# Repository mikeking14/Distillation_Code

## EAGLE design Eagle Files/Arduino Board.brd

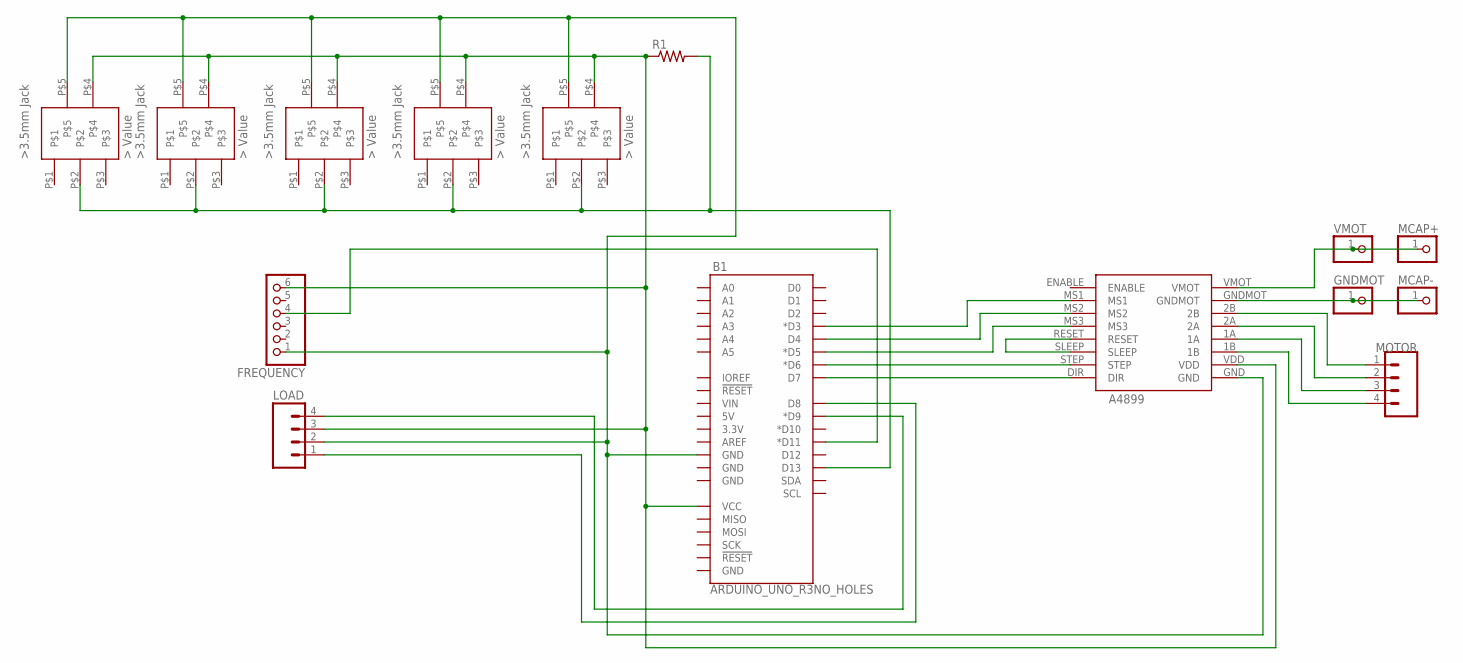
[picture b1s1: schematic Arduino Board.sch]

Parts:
3.5MM_JACK1, 3.5MM_JACK2, 3.5MM_JACK3, 3.5MM_JACK4, 3.5MM_JACK5: 3.5MM_JACK
A4899_1: A4899
B1: ARDUINO_UNO_R3NO_HOLES; ARDUINO_R3_NO_HOLES
FREQUENCY: PINHD-1X6; 1X06
GNDMOT: PINHD-1X1; 1X01
LOAD: M04PTH; 1X04
MCAP+: PINHD-1X1; 1X01
MCAP-: PINHD-1X1; 1X01
MOTOR: M04PTH; 1X04
R1: R-US_0204/5; 0204/5
VMOT: PINHD-1X1; 1X01

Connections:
unnamed: 3.5MM_JACK1.P$5, 3.5MM_JACK2.P$5, 3.5MM_JACK3.P$5, 3.5MM_JACK4.P$5, 3.5MM_JACK5.P$5, A4899_1.GND, B1.GND@4 (GND), FREQUENCY.1, LOAD.2
unnamed: 3.5MM_JACK1.P$2, 3.5MM_JACK2.P$2, 3.5MM_JACK3.P$2, 3.5MM_JACK4.P$2, 3.5MM_JACK5.P$2, B1.D13, R1.2
unnamed: A4899_1.1B, MOTOR.4
unnamed: B1.D11 (*D11), FREQUENCY.4
unnamed: B1.D9 (*D9), LOAD.4
unnamed: B1.D8, LOAD.1
unnamed: A4899_1.VMOT, MCAP+.1, VMOT.1
unnamed: A4899_1.GNDMOT, GNDMOT.1, MCAP-.1
unnamed: A4899_1.2B, MOTOR.1
unnamed: A4899_1.2A, MOTOR.2
unnamed: A4899_1.1A, MOTOR.3
unnamed: A4899_1.MS3, B1.D5 (*D5)
unnamed: A4899_1.RESET, A4899_1.SLEEP
unnamed: 3.5MM_JACK1.P$4, 3.5MM_JACK2.P$4, 3.5MM_JACK3.P$4, 3.5MM_JACK4.P$4, 3.5MM_JACK5.P$4, A4899_1.VDD, B1.VCC, FREQUENCY.6, LOAD.3, R1.1
unnamed: A4899_1.STEP, B1.D6 (*D6)
unnamed: A4899_1.DIR, B1.D7
unnamed: A4899_1.MS2, B1.D4
unnamed: A4899_1.MS1, B1.D3 (*D3)

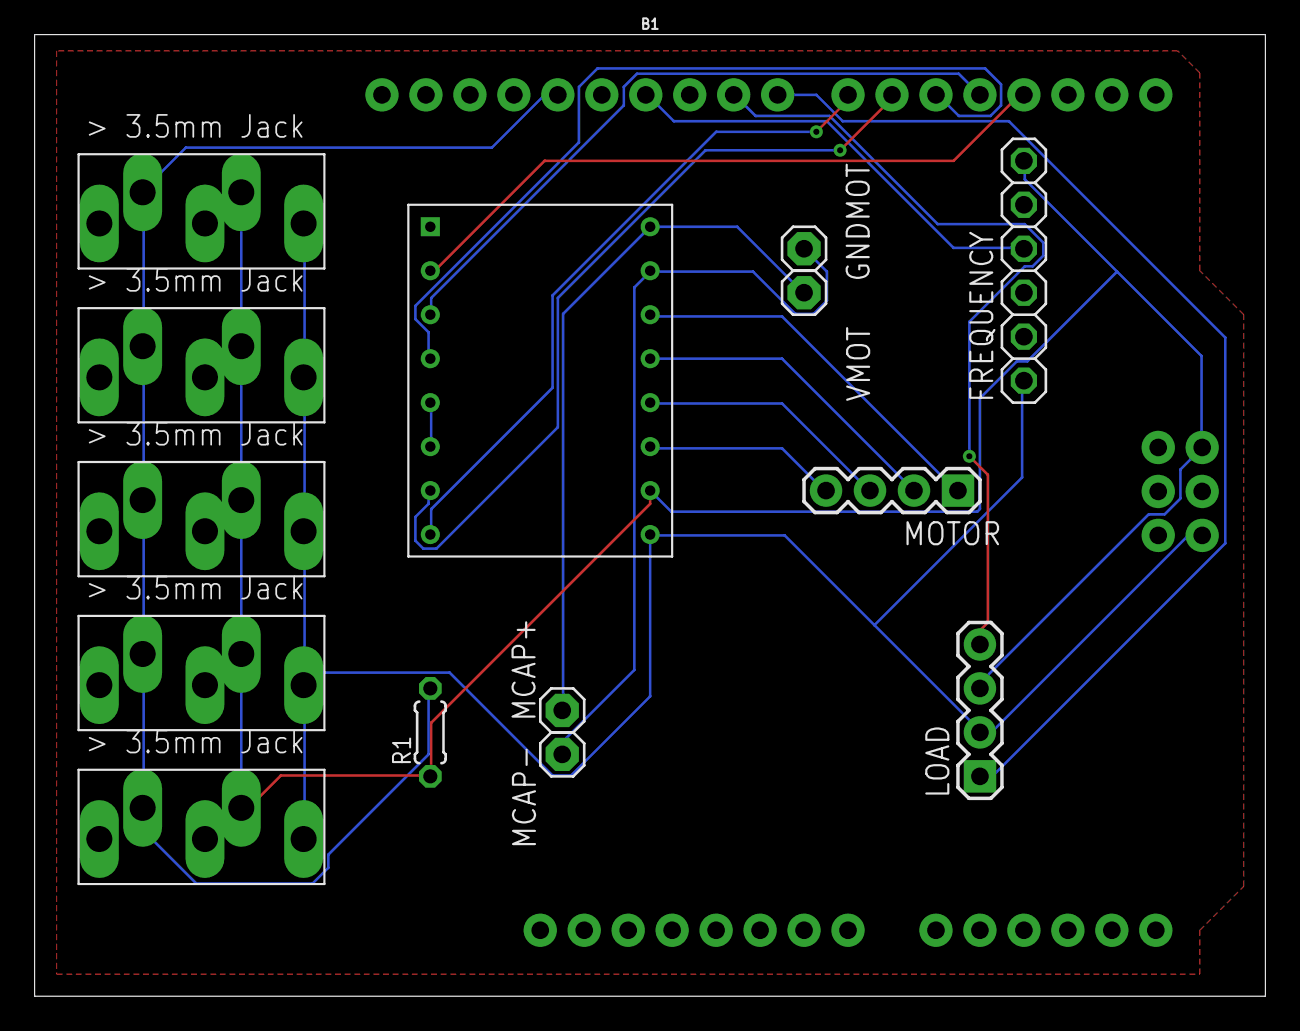
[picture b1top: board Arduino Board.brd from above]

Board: 2 copper layers, 71.1 x 55.5 mm, 15 parts (0 on the bottom side), 18 nets.

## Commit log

2019-07-30 Start of Platfomio Distillation Repo
2019-07-31 Added python script to LOG the Serial Output
2019-07-31 added file
2019-07-31 Update DistillationCode.ino
    Bug
2019-08-01 Formatting
2019-08-01 State awareness variable and ReadMe file added
2019-08-03 testing
2019-08-03 more testing
2019-08-03 end of testing
2019-08-06 //changing stuff
2019-08-07 Adding Useful_Arduino_Code.txt to place code from main CODE
2019-08-07 Commiting with Bugs
2019-08-08 Temperature Anomoly catcher caused main print to not occur
2019-08-08 Serial Print Bug
2019-08-08 Derivative calculation from towerTemp to towertempError
2019-08-08 Pretty sure Derivative is working now
2019-08-08 Adding extra code file
2019-08-08 PID_Testing-Merge
2019-08-08 Revert "PID_Testing-Merge"
    This reverts commit dfe529a43f6678775a1edac71378e7096a9a5ac8.
2019-08-13 Added Frequency Counter
2019-08-27 Distillation Run 32
2019-08-27 Added correct Temperature Device Addresses
2019-08-27 Bugs
2019-08-27 RE-Adding Checkpoint/Incrementer
2019-08-27 Distillation Run 32 V2
2019-08-27 Calibration Hx711 Files
2019-08-28 Distillation Run 32 v3
2019-08-28 Bug: PIDerror calculated from HeatExch. Fixed to towerTemp
2019-08-28 PWM + FreqCounter incompatible. Switched to using pin 6.
2019-08-29 Run 32 Data
2019-08-29 Distillation Run 33
2019-08-29 Distillation Run 33 v2
2019-08-30 DATA: Distillation Run 33* (Actually 34)
2019-09-03 Adding a DataProcessing folder for DATA and MATLAB files
2019-09-25 Distillation Run 35
2020-01-19 Computer Update: Trying to Sync with Jacob
2020-05-11 Cleanup
2020-05-12 Cleanup Tests
2020-05-19 Added Startup Procedure for flow control valve
2020-05-19 Start of Visual Studio
2020-05-19 Changing from .ino to .cpp
2020-05-19 Trying to Sync From Visual Studio
2020-05-21 Change Back to arudino file
2020-05-26 Adding Run File
2020-05-26 Converting TDSM to xlsx
2020-05-26 File Structure Edits
2020-05-27 Pre-Run 36
2020-05-28 Post Run 36
2020-05-28 Post Run 36.2
2020-06-06 Pre-Run 37
2020-06-06 Post Run 37
2020-06-06 Added plot to analyze PID controller & changed the P constant to 8
2020-06-07 Post Run 38 - Error in PID
2020-06-07 Post Run 38
2020-06-07 Pre Run 39
2020-06-07 Post Run 39
2020-06-10 Post Run 40 (Real)
2020-06-10 Pre Run 40
2020-06-16 Run 40 - data processing
2020-06-16 Getting rid of temperature anomoly counter
2020-06-16 Cleanup: Created printData() function
2020-06-16 Cleanup: created getMass() & startupSequence functions
2020-06-16 Cleanup: Created calculatePID() function
2020-06-16 Cleanup: Created temperatureIncrementer() function
2020-06-16 Cleanup: Moved #include to top of source file
2020-06-16 Cleanup: Fixed several variable formats
2020-06-16 Cleanup: Created getFrequency() function
    PS: comment formatting as well
2020-06-16 Cleanup: General Formatting
2020-06-18 Moved Variables to variable.h header file. Created getTemp() function
2020-06-19 State Awareness : Initial Testing
2020-06-22 Podt Run 41
2020-06-23 Updated things to do.
2020-06-23 Adding Map() function from PID to motorSetPosition()
2020-06-23 Change to Data importation format.
2020-06-24 -Startup sequence now records the MAX as well as MIN flow rate then uses map() function with PID -State Awareness implemented with if statements directly in loop
2020-06-24 Added Motor Stepper Motor Driver info.
2020-06-29 Post Run 42
2020-06-29 Reducing File Clutter
2020-06-30 Post Run 42 V2
2020-06-30 Fixing Issue with two separate state PID settings
2020-06-30 Update to Data Importation Format
2020-06-30 Post Run 42 Data Analysis Updates
2020-07-01 Post Run 43
2020-07-01 Change To min_mass_derivative
2020-07-14 Adding NI-DMM files
2020-07-15 Update to data-logging storage location
2020-07-16 Grammar update
2020-07-16 PID Integral Range increased to 15 from 10
2020-07-16 Post Run 44
2020-07-16 Update to Run 43 and 37
2020-07-23 Post Run 45
2020-07-23 Post Run 46
2020-08-06 Post Run 47
2020-08-07 Post Run 48.1
2020-08-11 Post Run 49
2020-08-12 Post Run 50
2020-08-12 Filename update
2020-08-12 Cache Update
2020-08-12 Adding Vertical lines for Methanol/IPA
2020-09-11 Post Run 51
2020-09-29 Distillation Code Update
2020-10-02 Adding Eagle Files
2020-11-06 Branching Off Main
    Branching off main so that I can cut things up and experiment, branches to be merged near completion.
2020-11-06 Revert "Branching Off Main"
2020-11-06 Adding DS_Store to .gitnore
2020-11-06 Update to Function and Variable file structure
2021-01-23 Multi Frequency Version 2
2021-01-23 Revert "Multi Frequency Version 2"
    This reverts commit 9eb2402d08a51911b17efd5ce4c995c4c3033c11.
2021-01-23 Adding Back MultiFreq
2021-01-23 Another Change
2021-01-25 Update .gitignore
    Now excluding Visual Studio Code and PlatformIO extensions and directories.
2021-01-25 Revert "Update .gitignore"
    This reverts commit adc24757b0bf6b6e832bb8710af3702a59011ac8.
2021-01-25 Update .gitignore
    Ignoring Visual Studio files and directories.
2021-01-25 Deleting junk
    Removed a bunch of system dependent junk.
2021-01-28 Including Dependencies in lib
    To make this code more portable the required libraries have now been added to lib/. Note that licence compliance should be checked before this repository is published.
2021-01-31 The .ini Update
    Added .ini file support, removed library examples from repo, people can check the library repos for the examples.
2021-01-31 Small Edits
2021-02-03 Small changes and bug fixes.
    settings.ini still not working correctly
2021-02-09 Frequency measurment workng.
    ini read is working, writing to ini still has errors. Next step is UI.
2021-04-13 insert comment here
2021-04-13 Beta Version 1.0
    This is a functional system with touch screen and all.
2021-04-14 Adding vscode Properties
2021-04-14 Multi freq v2 (#6)
    * Adding Back MultiFreq
    * Another Change
    * Update .gitignore
    Now excluding Visual Studio Code and PlatformIO extensions and directories.
    * Revert "Update .gitignore"
    This reverts commit adc24757b0bf6b6e832bb8710af3702a59011ac8.
2021-04-14 Delete .vscode directory
    Launch options should be set on deployed device.
2021-10-29 First Working Version

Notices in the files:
parts and their libraries:
SparkFun-Boards: Licensing: Creative Commons ShareAlike 4.0 International - https://creativecommons.org/licenses/by-sa/4.0
SparkFun-Connectors: Licensing: CC v3.0 Share-Alike You are welcome to use this library for commercial purposes.
